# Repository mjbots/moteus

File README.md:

# moteus brushless servo #

This contains full designs for the moteus brushless servo actuator,
including firmware and PCBs.

**WARNING**: This is not just a software project.  It includes designs
for moderately high power electronics.  It has not yet burned down my
(or anyone's that I know of) house, but there are no guarantees.

# Specifications #

| Name                   | r4.11        | r5         | c1         | n1          | x1          |
|------------------------|--------------|------------|------------|-------------|-------------|
| Voltage Input          | 10-44V       | 10-34V     | 10-51V     | 10-54V      | 10-54V      |
| Peak Electrical Power  | 900W @ 30V   | 600W @ 26V | 250W @ 28V | 1.3kW @ 36V | 1kW @ 36V   |
| Mass                   | 14.2g        | 10.0g      | 8.9g       | 14.6g       | 23.8g       |
| Control Rate           | 15-30kHz     | -          | -          | -           | -           |
| PWM Switching Rate     | 15-60kHz     | -          | -          | -           | -           |
| CPU                    | STM32G4      | -          | -          | -           | -           |
| Uncooled phase current | 12A          | 15A        | 5A         | 9A          | 25A         |
| Cooled phase current   | 32A          | 42A        | 14A        | 26A         | 62A         |
| Peak phase current     | 100A         | 100A       | 20A        | 100A        | 120A        |
| Communications         | 5Mbps CAN-FD | -          | -          | -           | -           |
| Dimensions             | 46x53mm      | 40x40x9mm  | 38x38x9mm  | 46x46x8mm   | 56x56x10mm  |

Assembled and tested boards can be purchased at: https://mjbots.com

# Directory structure #

* hw/ - hardware (mechanical and electrical designs)
  * controller/ - PCB design for moteus-r4.11
  * c1/ - PCB design for moteus-c1
  * n1/ - PCB design for moteus-n1
  * x1/ - PCB design for moteus-x1
* fw/ - firmware for brushless controller
* lib/ - client side software
* utils/ - diagnostic tools
* tools/ - bazel build configure
* docs/ - documentation

# Documentation #

* [Quick Start](https://mjbots.github.io/moteus/quick-start)
* [All Documentation](https://mjbots.github.io/moteus/)
* [Discord](https://discord.gg/W4hUpBb)

# Misc #

 * 

# How to support moteus development #

The easiest way to support development the moteus hardware and firmware is as follows:

1) Buy things from https://mjbots.com
2) Build awesome machines!

That's it!  If for some reason you want to go above and beyond, you can sponsor mjbots through github: https://github.com/sponsors/mjbots

# License #

All files contained in this repository, unless otherwise noted, are
available under an Apache 2.0 License:
https://www.apache.org/licenses/LICENSE-2.0

# Trademark #

mjbots Robotic Systems LLC owns and protects the "mjbots" and "moteus" trademarks in many jurisdictions.

If you want to use these names in your project or product, please read the [Trademark Policy](https://mjbots.com/trademark-policy)

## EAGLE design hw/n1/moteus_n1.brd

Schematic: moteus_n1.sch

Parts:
A: PAD16AWG_TERM; 16AWG_TERM
AUX1: SM08B-GHS-TB(LF)(SN); JST_SM08B-GHS-TB(LF)(SN); MPN SM08B-GHS-TB(LF)(SN)
AUX2: SM07B-GHS-TB(LF)(SN); JST_SM07B-GHS-TB(LF)(SN); MPN SM07B-GHS-TB(LF)(SN)
AUX2H: PH2X4
B: PAD16AWG_TERM; 16AWG_TERM
C: PAD16AWG_TERM; 16AWG_TERM
C1, C19, C20, C21, C22, C25, C26, C27, C28, C29: DNP; C0402
C2: 1uF 100V; C0805; MPN GCM21BC72A105KE36L
C3, C17, C18, C23\, C24: 1uF; C0603; MPN MF-CAP-0603-1uF
C4: 22uF; C1206; MPN GRM31CR71A226KE15L
C5, C11, C23, C41: 1uF; C0402; MPN MF-CAP-0402-1uF
C6: 22uF; C1206; MPN CL31B226KPHNNNE
C7, C8, C9, C12, C14, C15, C16, C30, C32, C33, C42, C87: 0.1uF; C0402; MPN MF-CAP-0402-0.1uF
C10: 4.7uF; C0603; MPN CL10A475KP8NNNC
C13: 10uF; C1206; MPN MF-CAP-1206-10uF
C31: 0.01uF; C0402; MPN MF-CAP-0402-0.01uF
C34, C35, C36: 1000pF; C0402; MPN MF-CAP-0402-1nF
C37, C39: 0.1uF 100V; C0603; MPN GCJ188R72A104KA01D
C38, C40: 1uF; C0603; MPN C1608X7R1E105K080AE
C43: 0.47uF 100V; C0805; MPN 08051C474KAT2A
C44, C45, C46: 0.1uF 100V; C1206; MPN 12061C104KAT2A
C47, C48: 4.7uF 100V; C1206; MPN GRJ31CC72A475KE01K
C49, C50, C51, C52, C53, C54, C55, C56, C57, C58, C59, C60, C61, C62, C63, C64, C65, C66, C67, C68, C69, C70, C71, C72, C73, C74, C75, C76, C77, C78, C79, C80, C81, C82, C83, C84, C85, C86: 4.7uF 100V; C1206_NOBORDER; MPN GRJ31CC72A475KE01K
CAN1, CAN2: JST-PH3; JST_S3B-PH-SM4-TB(LF)(SN); MPN S3B-PH-SM4-TB(LF)(SN)
CAN_DBG: 1X3
D1: MF-LED-0603-RED; LED0603
D2: MF-LED-0603-RED; LED0603; MPN MF-LED-0603-GREEN
D3, D4, D5, D6, D7, D8, D9, D10, D11, D13, D14, D15, D16: BAT41KFILM; SODFL1608X70N; MPN BAT41KFILM
D12: DIODE-DO214AA; DO214AA; MPN SMBJ51D-M3/I
D33, D50: PAD24AWG_PAD; 24AWG_PAD
DAC: PAD24AWG_PAD; 24AWG_PAD
DG1: PAD24AWG_PAD; 24AWG_PAD
DTR: PAD24AWG_PAD; 24AWG_PAD
DTX: PAD24AWG_PAD; 24AWG_PAD
J1, J2: XT30XT30PW_MALE; XT30PW_MALE; MPN XT30PW-M
J3: SM06B-GHS-TB(LF)(SN); JST_SM06B-GHS-TB(LF)(SN); MPN SM06B-GHS-TB(LF)(SN)
L1: SRN4018-220M; IND_BOURNS_SRN4018; MANUFACTURER_PART_NUMBER 74404042470
L2: 74479887222A; IND_1008_WE-PMI_WRE; MPN 74479887222A
M1, M2, M3, M4: MOUNT; M2.5MOUNT
Q1, Q3, Q5: TPH1R204PL_VIAS; SOP_ADVANCE_8_VIAS; MPN TPH2R408QM,L1Q
Q2, Q4, Q6: TPH1R204PLSOP_ADVANCE_8; SOP_ADVANCE_8; MPN TPH2R408QM,L1Q
R1, R3: DNP; R0402
R2, R15: 100k 1%; R0402; MPN RC0402FR-07100KL
R4, R5, R8, R9, R10, R11, R12, R13, R14: 100; R0402; MPN MF-RES-0402-100
R6, R7, R25, R26, R33, R34: 2k; R0402; MPN MF-RES-0402-2K
R16: 4.7k 1%; R0402; MPN RC0402FR-074K7L
R17: 47k NTC; R0402; MPN NCP15WB473F03RC
R18, R19: 10k 1%; R0402; MPN RC0402FR-0710KL
R20, R21: 560; R0402; MPN MF-RES-0402-560
R22, R23, R24: 22; R0402; MPN MF-RES-0402-22
R27, R28, R30, R31, R32: 7.5; R0402; MPN RC0402FR-077R5L
R29: 7.5; R0805; MPN RC0805FR-077R5L
R35, R36: 120; R0402; MPN RC0402FR-07120RL
R37: DNP; R0805
R38, R39, R40: 0; R0402; MPN MF-RES-0402-0
RA: 0.5mOhm 1% 2W; M1206; MPN HCS1206FTL500
RB: 0.5mOhm 1% 2W; M1206; MPN HCS1206FTL500
RC: 0.5mOhm 1% 2W; M1206; MPN HCS1206FTL500
SH1, SH2, SH3: SHORTT5; SHORT_TOP-50
SH4: SHORTMEDIUM; SHORT_TOP-MEDIUM
SWD: JST-ZH6; JST_S6B-ZR-SM4A-TF(LF)(SN); MPN S6B-ZR-SM4A-TF(LF)(SN)
TEMP: 1X2
U1: MAX15062BATA+T; 21-0487A_MXM; MANUFACTURER_PART_NUMBER MAX15062BATA+T
U2: ADP5301ACBZ-4-R7; BGA9C50P3X3_165X187X66; MPN ADP5301ACBZ-4-R7
U3: STM32G474CEU6; QFN50P700X700X60-49N; MPN STM32G474CEU6
U4: TCAN1042HGV; SOIC8; MPN TCAN1057AEVDRQ1
U5: AS5147; TSSOP14; MPN AS5047P-ATSM
U7: DRV8353S; WQFN-40; MPN DRV8353FSRTAR
U8: SN65HVD35DR; D14
VN: PAD16AWG_TERM; 16AWG_TERM
VP: PAD16AWG_TERM; 16AWG_TERM

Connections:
+3V3: AUX1.2, AUX2.2, AUX2H.P$4 (4), C6.P$1, C7.P$1, C8.P$1, C10.P$1, C11.P$1, C12.P$1, C13.P$2, C15.P$1, C16.P$1, C18.P$1, C23.P$1, C24.P$1, C30.P$1, C42.P$2, C87.P$1, D33.P$1, L2.1, R2.P$2, R17.P$1, R20.P$1, R21.P$1, R25.P$1, R26.P$1, R40.P$2, SWD.6, TEMP.1, U2.C2 (FB), U3.1 (VBAT), U3.20 (VREF+), U3.21 (VDDA), U3.23 (VDD_1), U3.35 (VDD_2), U3.48 (VDD_3), U4.5 (VIO), U5.12 (VDD3V), U7.24 (VREF), U8.13 (VCC_2), U8.14 (VCC)
+5V: AUX1.1, AUX2.1, AUX2H.P$2 (2), C4.P$1, C5.P$1, C14.P$1, C17.P$1, C23\.P$1, D50.P$1, J3.1, L1.1, R39.P$2, U1.4 (FB/VOUT), U2.A2 (PVIN), U2.A3 (EN), U4.3 (VCC)
AS5047_CS: U3.19 (PB2), U5.1 (CS/)
AUX1P_A: AUX1.3, R10.P$1
AUX1P_B: AUX1.4, R11.P$1
AUX1P_C: AUX1.5, R12.P$1
AUX1P_D: AUX1.6, R13.P$1
AUX1P_E: AUX1.7, R14.P$1
AUX1_A: C29.P$1, R10.P$2, U3.13 (PA5), U3.27 (PB14), U5.2 (CLK)
AUX1_B: C28.P$1, R11.P$2, U3.42 (PB4), U5.3 (MISO)
AUX1_C: C27.P$1, R12.P$2, U3.15 (PA7), U5.4 (MOSI)
AUX1_D: C26.P$1, DTR.P$1, R13.P$2, R34.P$2, U3.38 (PA15), U8.2 (R)
AUX1_E: C25.P$1, DTX.P$1, R14.P$2, R33.P$2, U3.41 (PB3), U3.47 (PB9), U8.5 (D)
AUX1_I2C_PULLUP: D13.2 (A), D14.2 (A), U3.46 (PB8-BOOT0)
AUX2P_A: AUX2.3, AUX2H.P$7 (7), AUX2H.P$8 (8), R4.P$1
AUX2P_B: AUX2.4, AUX2H.P$5 (5), R5.P$1
AUX2P_C: AUX2.5, AUX2H.P$3 (3), R9.P$1
AUX2P_D: AUX2.6, AUX2H.P$1 (1), R8.P$1
AUX2_A: C22.P$1, R4.P$2, U3.6 (PF1-OSC_OUT)
AUX2_B: C21.P$1, R5.P$2, R6.P$2, U3.5 (PF0-OSC_IN), U3.32 (PA10)
AUX2_C: C20.P$1, R7.P$2, R9.P$2, U3.16 (PC4), U3.33 (PA11)
AUX2_D: C19.P$1, R8.P$2, U3.45 (PB7)
AUX2_I2C_PULLUP: D15.2 (A), D16.2 (A), U3.34 (PA12)
CAN_N: CAN1.2, CAN2.2, CAN_DBG.2, R37.P$2, U4.6 (CANL)
CAN_P: CAN1.1, CAN2.1, CAN_DBG.1, R37.P$1, U4.7 (CANH)
CAN_RX: U3.43 (PB5), U4.4 (RXD)
CAN_TX: U3.44 (PB6), U4.1 (TXD)
CUR1: R22.P$1, U7.23 (SOA)
CUR2: R23.P$1, U7.22 (SOB)
CUR3: R24.P$1, U7.21 (SOC)
DAC: DAC.P$1, R2.P$1, R3.P$2, U3.12 (PA4)
DRV8323_CS: U3.17 (PB0), U7.30 (CS)
DRV8323_MISO: R25.P$2, U3.40 (PC11), U7.27 (MISO)
DRV8323_MOSI: U3.2 (PC13), U7.28 (MOSI)
DRV8323_SCLK: U3.39 (PC10), U7.29 (SCLK)
FCUR1: C34.P$1, R22.P$2, U3.11 (PA3)
FCUR2: C35.P$1, R23.P$2, U3.14 (PA6)
FCUR3: C36.P$1, R24.P$2, U3.18 (PB1)
GHA: D5.1 (K), R28.P$1, U7.6 (GHA)
GHA_D: D5.2 (A), Q1.4 (G), R28.P$2
GHB: D8.1 (K), R30.P$1, U7.15 (GHB)
GHB_D: D8.2 (A), Q3.4 (G), R30.P$2
GHC: D11.1 (K), R32.P$1, U7.16 (GHC)
GHC_D: D11.2 (A), Q5.4 (G), R32.P$2
GLA: D3.1 (K), R27.P$1, U7.8 (GLA)
GLA_D: D3.2 (A), D4.1 (K), Q2.4 (G), R27.P$2
GLB: D6.1 (K), R29.P$1, U7.13 (GLB)
GLB_D: D6.2 (A), D7.1 (K), Q4.4 (G), R29.P$2
GLC: D9.1 (K), R31.P$1, U7.18 (GLC)
GLC_D: D9.2 (A), D10.1 (K), Q6.4 (G), R31.P$2
GND: AUX1.8, AUX2.7, AUX2H.P$6 (6), C3.P$2, C4.P$2, C5.P$2, C6.P$2, C7.P$2, C8.P$2, C9.P$2, C10.P$2, C11.P$2, C12.P$2, C13.P$1, C14.P$2, C15.P$2, C16.P$2, C17.P$2, C18.P$2, C19.P$2, C20.P$2, C21.P$2, C22.P$2, C23.P$2, C23\.P$2, C24.P$2, C25.P$2, C26.P$2, C27.P$2, C28.P$2, C29.P$2, C30.P$2, C31.P$2, C32.P$2, C33.P$2, C34.P$2, C35.P$2, C36.P$2, C42.P$1, C87.P$2, CAN1.3, CAN2.3, CAN_DBG.3, DG1.P$1, J3.6, R3.P$1, R16.P$1, R18.P$2, R19.P$2, R38.P$1, SH4.2, SWD.4, U1.7 (GND), U2.B1 (PGND), U2.B2 (AGND), U3.49 (THERMALPAD), U4.2 (GND), U4.8 (STB), U5.5 (TEST), U5.13 (GND), U7.25 (AGND), U8.6 (GND_2), U8.7 (GND)
LED1: D1.CATHODE, U3.28 (PB15)
LED2: D2.CATHODE, U3.29 (PC6)
MOTOR1: U3.8 (PA0), U7.32 (INHA)
MOTOR2: U3.9 (PA1), U7.34 (INHB)
MOTOR3: U3.10 (PA2), U7.36 (INHC)
MOTOR_ENABLE: U3.3 (PC14-OSC32_IN), U7.31 (ENABLE)
MOTOR_FAULT: R26.P$2, U3.26 (PB13), U7.26 (FAULT)
MOTOR_HIZ: U3.4 (PC15-OSC32_OUT), U7.33 (INLA), U7.35 (INLB), U7.37 (INLC)
unnamed: C1.P$1, M3.P$1, R1.P$1
unnamed: C40.P$2, U7.40 (VGLS)
unnamed: R40.P$1, U5.11 (VDD5V)
unnamed: C3.P$1, U1.3 (VCC)
unnamed: L2.2, U2.A1 (SW)
unnamed: C39.P$2, U7.1 (CPL)
unnamed: C39.P$1, U7.2 (CPH)
unnamed: C38.P$2, U7.5 (VCP)
unnamed: C41.P$2, U7.38 (DVDD)
unnamed: D1.ANODE, R20.P$2
unnamed: D2.ANODE, R21.P$2
unnamed: R38.P$2, U1.5 (MODE)
unnamed: D14.1 (K), R34.P$1
unnamed: R39.P$1, U2.B3 (SYNC/_MODE)
unnamed: D13.1 (K), R33.P$1
unnamed: D15.1 (K), R6.P$1
unnamed: D16.1 (K), R7.P$1
NRST: C9.P$1, SWD.2, U3.7 (PG10-NRST)
RS422_A: J3.2, R35.P$2, U8.12 (A)
RS422_B: J3.3, R35.P$1, U8.11 (B)
RS422_DE: U3.24 (PB11), U8.4 (DE)
RS422_RE: U3.22 (PB10), U8.3 (!RE)
RS422_Y: J3.4, R36.P$2, U8.9 (Y)
RS422_Z: J3.5, R36.P$1, U8.10 (Z)
SHA: A.1, A.2, A.3, A.4, A.5, A.6, A.7, A.8, A.9, A.10, A.11, A.12, A.13, Q1.1 (S), Q1.2 (S), Q1.3 (S), Q2.5 (D), Q2.6 (D), Q2.7 (D), Q2.8 (D), Q2.PAD (D), U7.7 (SHA)
SHB: B.1, B.2, B.3, B.4, B.5, B.6, B.7, B.8, B.9, B.10, B.11, B.12, B.13, Q3.1 (S), Q3.2 (S), Q3.3 (S), Q4.5 (D), Q4.6 (D), Q4.7 (D), Q4.8 (D), Q4.PAD (D), U7.14 (SHB)
SHC: C.1, C.2, C.3, C.4, C.5, C.6, C.7, C.8, C.9, C.10, C.11, C.12, C.13, Q5.1 (S), Q5.2 (S), Q5.3 (S), Q6.5 (D), Q6.6 (D), Q6.7 (D), Q6.8 (D), Q6.PAD (D), U7.17 (SHC)
SWCLK: SWD.5, U3.37 (PA14)
SWDIO: SWD.3, U3.36 (PA13)
SXA_N: SH1.1, U7.10 (SNA)
SXA_P: C44.P$2, Q2.1 (S), Q2.2 (S), Q2.3 (S), RA.2, U7.9 (SPA)
SXB_N: SH2.1, U7.11 (SNB)
SXB_P: C45.P$2, Q4.1 (S), Q4.2 (S), Q4.3 (S), RB.2, U7.12 (SPB)
SXC_N: SH3.1, U7.20 (SNC)
SXC_P: C46.P$2, Q6.1 (S), Q6.2 (S), Q6.3 (S), RC.2, U7.19 (SPC)
V+: C2.P$1, C37.P$1, C38.P$1, C43.P$1, C44.P$1, C45.P$1, C46.P$1, C47.P$1, C48.P$1, C49.P$1, C50.P$1, C51.P$1, C52.P$1, C53.P$1, C54.P$1, C55.P$1, C56.P$1, C57.P$1, C58.P$1, C59.P$1, C60.P$1, C61.P$1, C62.P$1, C63.P$1, C64.P$1, C65.P$1, C66.P$1, C67.P$1, C68.P$1, C69.P$1, C70.P$1, C71.P$1, C72.P$1, C73.P$1, C74.P$1, C75.P$1, C76.P$1, C77.P$1, C78.P$1, C79.P$1, C80.P$1, C81.P$1, C82.P$1, C83.P$1, C84.P$1, C85.P$1, C86.P$1, D12.C, J1.1, J2.1, Q1.5 (D), Q1.6 (D), Q1.7 (D), Q1.8 (D), Q1.PAD (D), Q3.5 (D), Q3.6 (D), Q3.7 (D), Q3.8 (D), Q3.PAD (D), Q5.5 (D), Q5.6 (D), Q5.7 (D), Q5.8 (D), Q5.PAD (D), R15.P$2, U1.1 (VIN), U1.2 (EN/UVLO), U7.3 (VM), U7.4 (VDRAIN), VP.1, VP.2, VP.3, VP.4, VP.5, VP.6, VP.7, VP.8, VP.9, VP.10, VP.11, VP.12, VP.13
V-: C1.P$2, C2.P$2, C37.P$2, C40.P$1, C41.P$1, C43.P$2, C47.P$2, C48.P$2, C49.P$2, C50.P$2, C51.P$2, C52.P$2, C53.P$2, C54.P$2, C55.P$2, C56.P$2, C57.P$2, C58.P$2, C59.P$2, C60.P$2, C61.P$2, C62.P$2, C63.P$2, C64.P$2, C65.P$2, C66.P$2, C67.P$2, C68.P$2, C69.P$2, C70.P$2, C71.P$2, C72.P$2, C73.P$2, C74.P$2, C75.P$2, C76.P$2, C77.P$2, C78.P$2, C79.P$2, C80.P$2, C81.P$2, C82.P$2, C83.P$2, C84.P$2, C85.P$2, C86.P$2, D4.2 (A), D7.2 (A), D10.2 (A), D12.A, J1.2, J2.2, R1.P$2, RA.1, RB.1, RC.1, SH1.2, SH2.2, SH3.2, SH4.1, U7.39 (GND), U7.PAD, VN.1, VN.2, VN.3, VN.4, VN.5, VN.6, VN.7, VN.8, VN.9, VN.10, VN.11, VN.12, VN.13
VBAT_SENSE: C31.P$1, R15.P$1, R16.P$2, U3.31 (PA9)
VSW: L1.2, U1.8 (LX)
VTEMP_FET: C32.P$1, R17.P$2, R18.P$1, U3.25 (PB12)
VTEMP_MOT: C33.P$1, R19.P$1, TEMP.2, U3.30 (PA8)

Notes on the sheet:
PCB rev divider HI / LO r1.1/r1.2 - open / 100k r1.3 - 100k / open

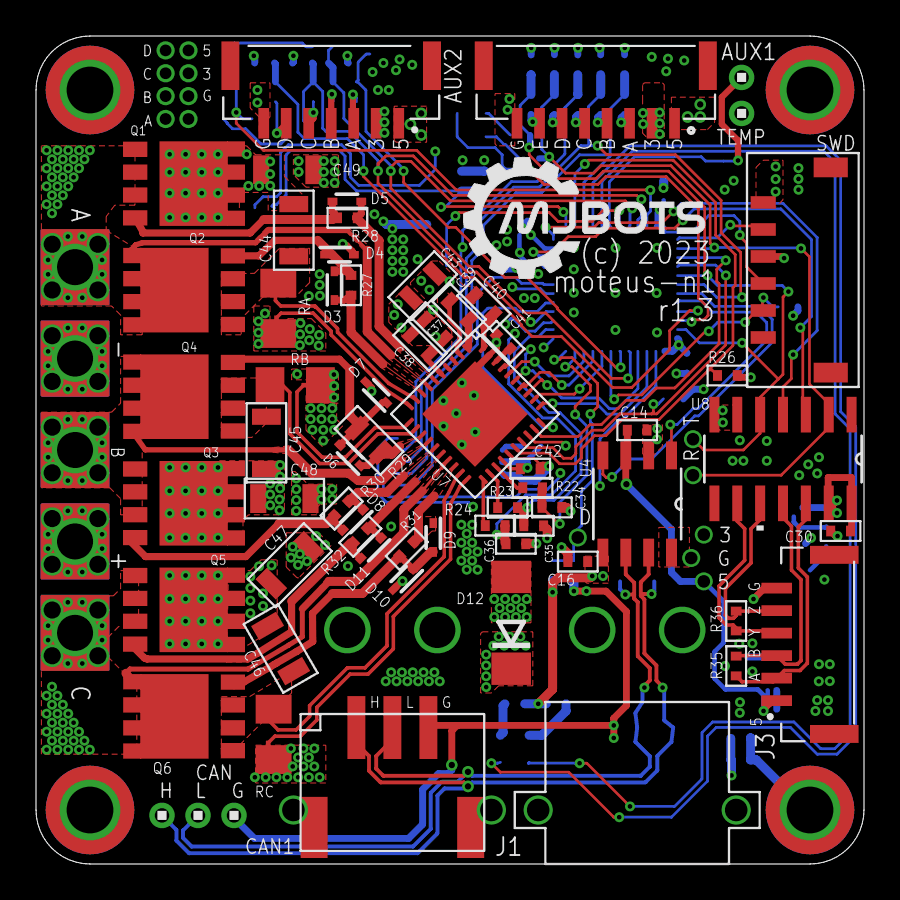
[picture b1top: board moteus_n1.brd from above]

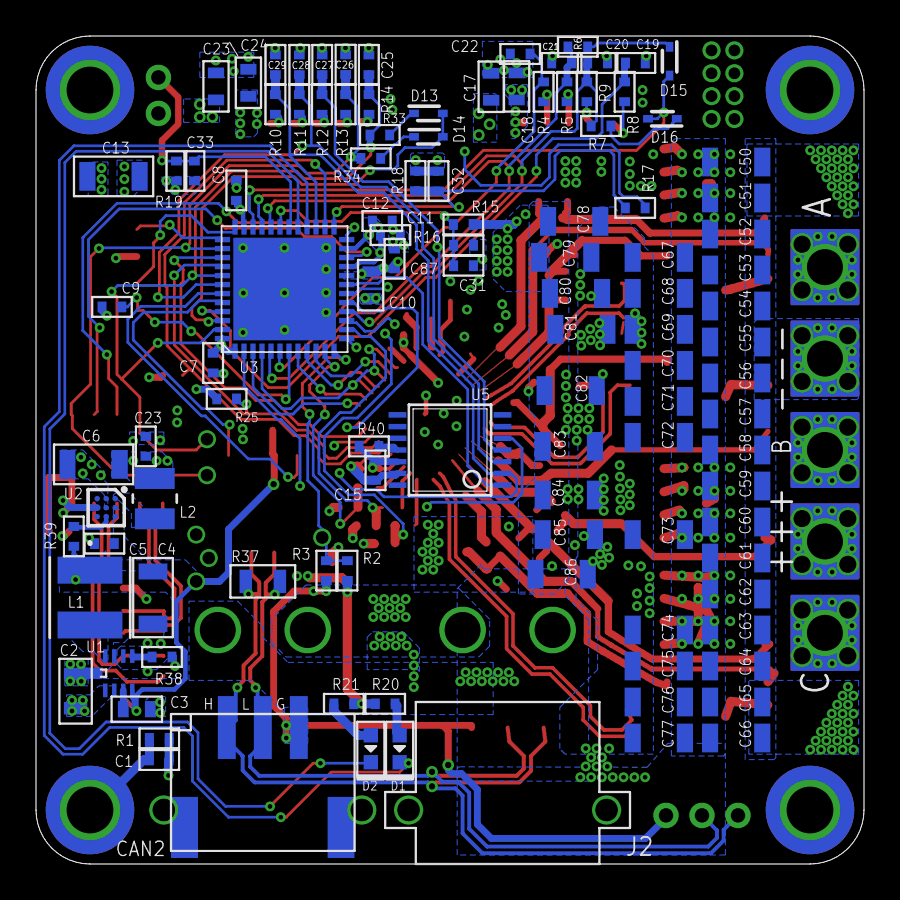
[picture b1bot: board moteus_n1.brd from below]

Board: 4 copper layers, 46.0 x 46.0 mm, 192 parts (117 on the bottom side), 100 nets.

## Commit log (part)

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2026-05-15 Add jerk-limited online trajectory generation
    When data->jerk_limit is finite and positive, the position trajectory
    generator slews control_acceleration at no more than the configured
    rate per second, producing an S-curve velocity profile instead of a
    bang-bang trapezoidal one. The behavior reduces to the legacy path
    when jerk_limit is NaN, so out-of-the-box trajectories are unchanged.
    This is not a complete substitute for systems like ruckig, notably:
2026-05-15 Tighten bounds across jerk-related tests
    Replace generous safety factors with empirically-derived tight
    bounds. Tightening summary:
    - ResidualBound: 10x -> 1x safety factor over the analytical
    (kinematic_floor + drift_floor). Worst observed across all jerk
    tests is ~30% of the unscaled bound, so 1x retains >3x headroom.
    - JerkBoundFor + the duplicate in RunAndCheckJerkBound + the in-line
2026-05-15 Verify jerk-bound per cycle in JerkLimitedTakesLongerThanTrapezoidal
    The comment claimed the jerk-limited run should have no |Δa| > j*dt
    per cycle, but no such assertion existed. Add it: the run lambda
    now captures control_acceleration each cycle and (for the
    jerk-limited variant only) asserts |Δa| <= j*dt + accel*eps.
    Verified by replacing SlewAcceleration's per-cycle clamp with 2x the
    bound; the new check fires immediately (1.33 > 0.667).
2026-05-15 Test consolidation pass 2: subsume parameterizable singletons
    Three more groups subsumed into existing or new sweeps. Each
    consolidation was verified by reverting the relevant fix and
    confirming the consolidated test still catches the regression.
    Section E (mid-slew retargeting):
    - Extend JerkLimitRetargetAtEachPhase to accept `new_target`
    per row (was hard-coded 10.0) and to recognise `delay < 0`
2026-05-15 Stop NaN'ing data->position at jerk-limited termination
    The previous fix (c394983a) made the trajectory_done reset
    conditional on the commit latch -- but only protected the cycle
    the host frame actually arrived on. In production the host polls
    every ~2 ms, leaving ~60 ISR cycles between frames during which the
    FW used to NaN'd data->position out of the just-completed
    trajectory. The latch tolerance check (data->position == cp) then
2026-05-16 Add termination sweeps for four previously-uncovered scenarios
    Four new tests covering scenarios that production failures suggest
    the original tests do not exercise:
    - JerkLimitMoveLoopTermination: the moteus.move_to() loop pattern
    (a sequence of four same/different targets across two channels,
    three iterations). Catches any failure where consecutive moves
    to the same target oscillate or fail to terminate -- the exact
2026-05-16 Add hall lost-tracking recovery for stuck misaligned motors
    When hall sensors are physically misaligned (sector widths not
    uniformly 60° electrical), the firmware's filtered_value can coast
    forward to compensated + max_err during the wider sectors and then
    stay there once the motor stops -- with no transition to "reset"
    commutation, the firmware-reported electrical angle can sit nearly
    90° from the rotor's true angle, the projected q-axis torque
2026-05-19 Deployed 39e1a6a with MkDocs version: 1.6.1
2026-05-19 Do a better job estimating the ground truth hall position
    The find_ground_truth function used to return the start of a sector
    and velocity=0 when either the trace ended or when the rotor bounced
    back and forth.
    Instead, for end of trace return the center of the sector, and if the
    rotor bounced back and forth, return the boundary itself, as we have
    no real indication that it went into the sector at all.
2026-05-21 Deployed ad43136 with MkDocs version: 1.6.1
2026-05-21 Actually update CHANGELOG.md since the last release
2026-05-22 Deployed e1333e5 with MkDocs version: 1.6.1
2026-05-23 Fix more doc config typos
2026-05-23 Rewrite mypy_test to operate on the build files
    Previously it generated a fake version file in the actual source tree
    which was often left behind.
2026-05-24 Deployed eb7c5fc with MkDocs version: 1.6.1
2026-05-24 Deployed e4459e7 with MkDocs version: 1.6.1
2026-05-24 Release python 1.0.0rc2
2026-05-25 Release python 1.0.0rc3
2026-05-25 Release python 1.0.0rc4
2026-05-27 Fix multiple gate drive strength mapping issues and re-tune the n1
    There were two separate bugs in involved here.
    1. For drv8353 boards, we were accidentally using the gate mapping
    table for idrivep on the low side when we should have been using
    idriven.
    2. We were mis-characterizing moteus-c1 as a drv8353 board and have
    been mis-characterizing moteus-n1 as a drv8323 board since the
2026-05-28 Release python 1.0.0
2026-06-03 Fix the location of the default UART port
    The intention was that the default UART port would always be present
    on pins that were connectorized. That is what is documented.
    However, the actual implementation of this was broken, and moteus-c1
    got its default UART on aux1, whereas moteus-n1 got it on aux2. Swap
    those back to what was intended.
    Now, the default UARTs are at:
2026-06-03 Deployed ae2d7a77 with MkDocs version: 1.6.1
2026-06-03 Rust API: Fix MSRV to 1.75 (was incorrectly set to 1.85)
2026-06-03 Rust API: Fix version numbers in docs/integration/rust.md
2026-06-03 Rust API: Add Transport::from_device() for single-device construction
2026-06-03 Rust API: Use fixed-size arrays instead of Vec for single-request cycles
2026-06-03 Rust API: Add AsyncController
    - AsyncController: High-level async interface using tokio feature
    - Full module exports in lib.rs
2026-06-03 Rust API: Rename Request builder methods with with_ prefix
2026-06-03 Rust API: Add SocketCAN transport for Linux
    Add SocketCAN transport for native Linux CAN interfaces:
    - SocketCan: Linux kernel CAN interface support
    - CAN-FD frame send/receive
    - Interface enumeration
2026-06-03 Rust API: Fix all cargo clippy warnings
    Applied automatic fixes and manual corrections for: unnecessary casts
    left over from f64->f32 migration, doc comment overindentation,
    map_or -> is_none_or/is_some_and, derivable Default impl for
    FrameFilter, while_let_loop, iter().copied().collect() -> to_vec(),
    and suppressed needless_range_loop where refactoring would reduce
    readability.
2026-06-03 Rust API: Add #[non_exhaustive] to all public structs and enums
    Prevents future field or variant additions from being breaking changes
    for external crate users. Internal code is unaffected.
2026-06-03 Rust API: Fix moteus-protocol feature documentation
2026-06-03 Rust API: Revert edition to 2021 to preserve MSRV 1.75
2026-06-03 Rust API: Simplify Explicit Transport doc example
2026-06-03 Rust API: Fix SocketCanFactory references for cross-platform builds
    Cfg-gate get_factories(), get_async_factories(), and related tests
    that reference SocketCanFactory/AsyncSocketCanFactory so they only
    compile on Linux. This fixes builds on non-Linux platforms.
2026-06-03 Rust API: Add doc tests to bazel test suite, convert ignore to no_run
    Add rust_doc_test targets for both base and all-features variants.
    Convert all `ignore` doctests to `no_run` (compiled but not executed)
    where possible, and fix doc examples to compile correctly. Only 3
    examples remain `ignore` in the base target (require tokio/clap
    features) but are tested by the all-features variant.
2026-06-03 Rust API: Trim root re-exports to core types only
    Reduce the moteus crate root from ~46 re-exports to ~12 core types
    that most users need. Advanced types remain accessible through their
    public modules (e.g., moteus::diagnostic::DiagnosticStream,
    moteus::transport::transaction::Request). This makes auto-complete
    more useful and the API surface easier to understand.
2026-06-03 Rust API: Remove SocketCan stubs on non-Linux, cfg-gate factory impls
    SocketCan is only available on Linux. Rather than providing stub types
    that fail at runtime, cfg-gate the struct, factory impl, and registry
    entry so they simply don't exist on non-Linux platforms.
2026-06-03 Rust API: Add #[must_use] to derived setter methods
2026-06-03 Rust API: Make multiplex module pub(crate), keep scaling public
    The multiplex module's types are re-exported at the crate root; the
    raw protocol command byte constants are also re-exported for users who
    need them. The scaling module stays public since users interact with
    scaling consts directly via Value::to_f32().
2026-06-03 rust: Rename transport structures to match python more closely
    - the structures that directly communicate with a device now get a
    'Device' suffix like in python
    - the TransportOps trait is now Transport
    - the Transport struct is now Router
    Then, there are new wrappers named 'Fdcanusb' and 'SocketCan' which
    are a 'Router' that is composed of a single device of the given type.
2026-06-03 Rust API: Add transport registry for external factory registration
    External crates can now register transport factories via register() and
    register_async() so they participate in auto-detection. Adds extra field
    to TransportOptions for transport-specific key-value args, moves
    factory-specific arg specs into arg_specs() trait methods, and replaces
    static TRANSPORT_ARG_SPECS with dynamic transport_arg_specs().
2026-06-03 rust: Add separate READMEs for each crate
2026-06-03 Reset I2C peripherals that appear to be taking too long
    If the STM32 I2C peripheral attempts to start a transaction with when
    both lines read low, it will itself hold both lines low, wedging with
    no way to get unstuck. Thus we use a brute-force timeout to reset the
    peripheral if a response doesn't come in on time.
2026-06-03 Deployed 46ca6586 with MkDocs version: 1.6.1
2026-06-10 Bump bytes from 1.11.0 to 1.11.1 in /lib/rust
    Bumps [bytes](https://github.com/tokio-rs/bytes) from 1.11.0 to 1.11.1.
    - [Release notes](https://github.com/tokio-rs/bytes/releases)
    - [Changelog](https://github.com/tokio-rs/bytes/blob/master/CHANGELOG.md)
    - [Commits](https://github.com/tokio-rs/bytes/compare/v1.11.0...v1.11.1)
    ---
    updated-dependencies:
2026-06-10 Deployed 0b3c7768 with MkDocs version: 1.6.1
2026-06-10 Deployed a30c3116 with MkDocs version: 1.6.1
2026-06-10 rust: Normalize capitalization of fdcanusb
2026-06-13 Deployed 3f62e5ed with MkDocs version: 1.6.1
2026-06-17 rust: Improvements to support out-of-crate transports
    Specifically, these changes are in service of eventual pi3hat support,
    which needs to have parent transports with no ability to communicate
    at all, but that merely contain children.
    Also, provide a mechanism for ArgSpec to be created from outside the
    crate.
2026-06-17 Deployed c84da142 with MkDocs version: 1.6.1
2026-06-17 Do a better job reporting how much space the disk cleanup saves
2026-06-17 Remove some stale documentation text about velocity mode
    There is a full example just below which is not stale, so there is no
    real reason to have this here anymore.
2026-06-17 Deployed 421fd6e6 with MkDocs version: 1.6.1
2026-06-17 Clarify that we are using bazel platforms
2026-06-17 Deployed e75764d0 with MkDocs version: 1.6.1
2026-06-18 debug: emit control_velocity in high-rate debug (bit 28)
2026-06-18 Deployed 7b4e6c9c with MkDocs version: 1.6.1
2026-06-25 First draft of mjuart
    This is just a simple FT231XQ breakout board with a ZH4 connector to
    be used as a high rate UART adapter with moteus controllers. It can
    receive data from the high rate debug port at 3Mbps or be used at
    1Mbps to command and monitor.
2026-06-25 mjuart: Define soldermask colors

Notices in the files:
hw/controller/controller.sch:
Licensed under the Apache 2.0 License
hw/controller/r4.11/controller_tcan334gdcnt.brd:
(c) 2022
hw/controller/r4.3/controller.brd:
(c) 2020
hw/n1/moteus_n1.brd:
(c) 2023
parts and their libraries:
power_dist: COPYRIGHT: Copyright (C) 2018 Accelerated Designs. All rights reserved
COPYRIGHT: Copyright (C) 2022 Ultra Librarian. All rights reserved.
COPYRIGHT: Copyright (C) 2023 Ultra Librarian. All rights reserved.
